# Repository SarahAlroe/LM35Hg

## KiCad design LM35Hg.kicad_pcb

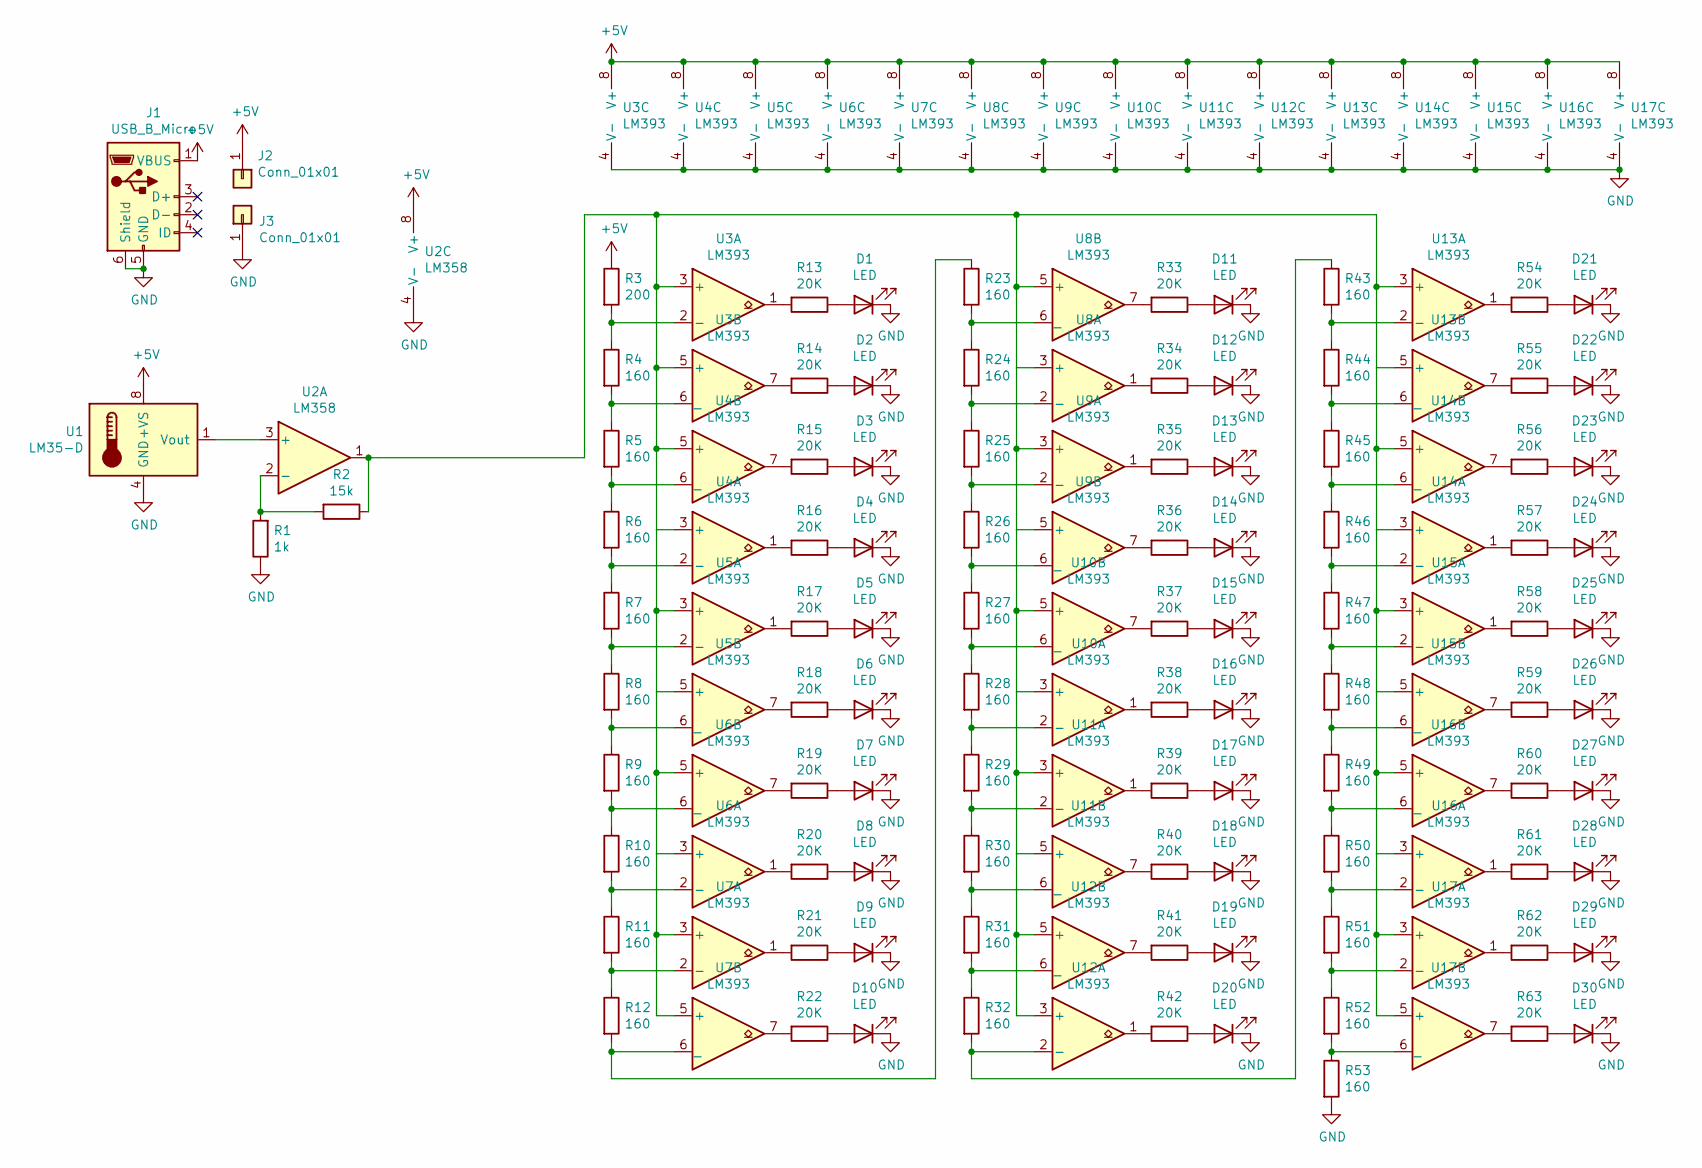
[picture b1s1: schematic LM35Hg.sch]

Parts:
D1, D2, D3, D4, D5, D6, D7, D8, D9, D10, D11, D12, D13, D14, D15, D16, D17, D18, D19, D20, D21, D22, D23, D24, D25, D26, D27, D28, D29, D30: LED; R_1206_3216Metric
J1: USB_B_Micro; USB_Micro-B_Molex-105017-0001
J2, J3: Conn_01x01; PinSocket_1x01_P2.54mm_Vertical
R1: 1k; R_1206_3216Metric
R2: 15k; R_1206_3216Metric
R3: 200; R_1206_3216Metric
R4, R5, R6, R7, R8, R9, R10, R11, R12, R23, R24, R25, R26, R27, R28, R29, R30, R31, R32, R43, R44, R45, R46, R47, R48, R49, R50, R51, R52, R53: 160; R_1206_3216Metric
R13, R14, R15, R16, R17, R18, R19, R20, R21, R22, R33, R34, R35, R36, R37, R38, R39, R40, R41, R42, R54, R55, R56, R57, R58, R59, R60, R61, R62, R63: 20K; R_1206_3216Metric
U1: LM35-D; SOIC-8_3.9x4.9mm_P1.27mm
U2: LM358; SOP-8_3.9x4.9mm_P1.27mm
U3, U4, U5, U6, U7, U8, U9, U10, U11, U12, U13, U14, U15, U16, U17: LM393; SOP-8_3.9x4.9mm_P1.27mm

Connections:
+5V: J1.1 (VBUS), J2.1, R3.1, U1.8 (+VS), U2.8 (V+), U3.8 (V+), U4.8 (V+), U5.8 (V+), U6.8 (V+), U7.8 (V+), U8.8 (V+), U9.8 (V+), U10.8 (V+), U11.8 (V+), U12.8 (V+), U13.8 (V+), U14.8 (V+), U15.8 (V+), U16.8 (V+), U17.8 (V+)
GND: D1.1 (K), D2.1 (K), D3.1 (K), D4.1 (K), D5.1 (K), D6.1 (K), D7.1 (K), D8.1 (K), D9.1 (K), D10.1 (K), D11.1 (K), D12.1 (K), D13.1 (K), D14.1 (K), D15.1 (K), D16.1 (K), D17.1 (K), D18.1 (K), D19.1 (K), D20.1 (K), D21.1 (K), D22.1 (K), D23.1 (K), D24.1 (K), D25.1 (K), D26.1 (K), D27.1 (K), D28.1 (K), D29.1 (K), D30.1 (K), J1.5 (GND), J1.6 (Shield), J3.1, R1.1, R53.2, U1.4 (GND), U2.4 (V-), U3.4 (V-), U4.4 (V-), U5.4 (V-), U6.4 (V-), U7.4 (V-), U8.4 (V-), U9.4 (V-), U10.4 (V-), U11.4 (V-), U12.4 (V-), U13.4 (V-), U14.4 (V-), U15.4 (V-), U16.4 (V-), U17.4 (V-)
unnamed: D1.2 (A), R13.1
unnamed: D2.2 (A), R14.1
unnamed: D3.2 (A), R15.1
unnamed: D4.2 (A), R16.1
unnamed: D5.2 (A), R17.1
unnamed: D6.2 (A), R18.1
unnamed: D7.2 (A), R19.1
unnamed: D8.2 (A), R20.1
unnamed: D9.2 (A), R21.1
unnamed: D10.2 (A), R22.1
unnamed: D11.2 (A), R33.1
unnamed: D12.2 (A), R34.1
unnamed: D13.2 (A), R35.1
unnamed: D14.2 (A), R36.1
unnamed: D15.2 (A), R37.1
unnamed: D16.2 (A), R38.1
unnamed: D17.2 (A), R39.1
unnamed: D18.2 (A), R40.1
unnamed: D19.2 (A), R41.1
unnamed: D20.2 (A), R42.1
unnamed: D21.2 (A), R54.1
unnamed: D22.2 (A), R55.1
unnamed: D23.2 (A), R56.1
unnamed: D24.2 (A), R57.1
unnamed: D25.2 (A), R58.1
unnamed: D26.2 (A), R59.1
unnamed: D27.2 (A), R60.1
unnamed: D28.2 (A), R61.1
unnamed: D29.2 (A), R62.1
unnamed: D30.2 (A), R63.1
unnamed: R1.2, R2.2, U2.2 (-)
unnamed: R2.1, U2.1, U3.3 (+), U3.5 (+), U4.3 (+), U4.5 (+), U5.3 (+), U5.5 (+), U6.3 (+), U6.5 (+), U7.3 (+), U7.5 (+), U8.3 (+), U8.5 (+), U9.3 (+), U9.5 (+), U10.3 (+), U10.5 (+), U11.3 (+), U11.5 (+), U12.3 (+), U12.5 (+), U13.3 (+), U13.5 (+), U14.3 (+), U14.5 (+), U15.3 (+), U15.5 (+), U16.3 (+), U16.5 (+), U17.3 (+), U17.5 (+)
unnamed: R3.2, R4.1, U3.2 (-)
unnamed: R4.2, R5.1, U3.6 (_)
unnamed: R5.2, R6.1, U4.6 (_)
unnamed: R6.2, R7.1, U4.2 (-)
unnamed: R7.2, R8.1, U5.2 (-)
unnamed: R8.2, R9.1, U5.6 (_)
unnamed: R9.2, R10.1, U6.6 (_)
unnamed: R10.2, R11.1, U6.2 (-)
unnamed: R11.2, R12.1, U7.2 (-)
unnamed: R12.2, R23.1, U7.6 (_)
unnamed: R13.2, U3.1
unnamed: R14.2, U3.7
unnamed: R15.2, U4.7
unnamed: R16.2, U4.1
unnamed: R17.2, U5.1
unnamed: R18.2, U5.7
unnamed: R19.2, U6.7
unnamed: R20.2, U6.1
unnamed: R21.2, U7.1
unnamed: R22.2, U7.7
unnamed: R23.2, R24.1, U8.6 (_)
unnamed: R24.2, R25.1, U8.2 (-)
unnamed: R25.2, R26.1, U9.2 (-)
unnamed: R26.2, R27.1, U9.6 (_)
unnamed: R27.2, R28.1, U10.6 (_)
unnamed: R28.2, R29.1, U10.2 (-)
unnamed: R29.2, R30.1, U11.2 (-)
unnamed: R30.2, R31.1, U11.6 (_)
unnamed: R31.2, R32.1, U12.6 (_)
unnamed: R32.2, R43.1, U12.2 (-)
unnamed: R33.2, U8.7
unnamed: R34.2, U8.1
unnamed: R35.2, U9.1
unnamed: R36.2, U9.7
unnamed: R37.2, U10.7
unnamed: R38.2, U10.1
unnamed: R39.2, U11.1
unnamed: R40.2, U11.7
unnamed: R41.2, U12.7
unnamed: R42.2, U12.1
unnamed: R43.2, R44.1, U13.2 (-)
unnamed: R44.2, R45.1, U13.6 (_)
unnamed: R45.2, R46.1, U14.6 (_)
unnamed: R46.2, R47.1, U14.2 (-)
unnamed: R47.2, R48.1, U15.2 (-)
unnamed: R48.2, R49.1, U15.6 (_)
unnamed: R49.2, R50.1, U16.6 (_)
unnamed: R50.2, R51.1, U16.2 (-)
unnamed: R51.2, R52.1, U17.2 (-)
unnamed: R52.2, R53.1, U17.6 (_)
unnamed: R54.2, U13.1
unnamed: R55.2, U13.7
unnamed: R56.2, U14.7
unnamed: R57.2, U14.1
unnamed: R58.2, U15.1
unnamed: R59.2, U15.7
unnamed: R60.2, U16.7
unnamed: R61.2, U16.1
unnamed: R62.2, U17.1
unnamed: R63.2, U17.7
unnamed: U1.1 (Vout), U2.3 (+)

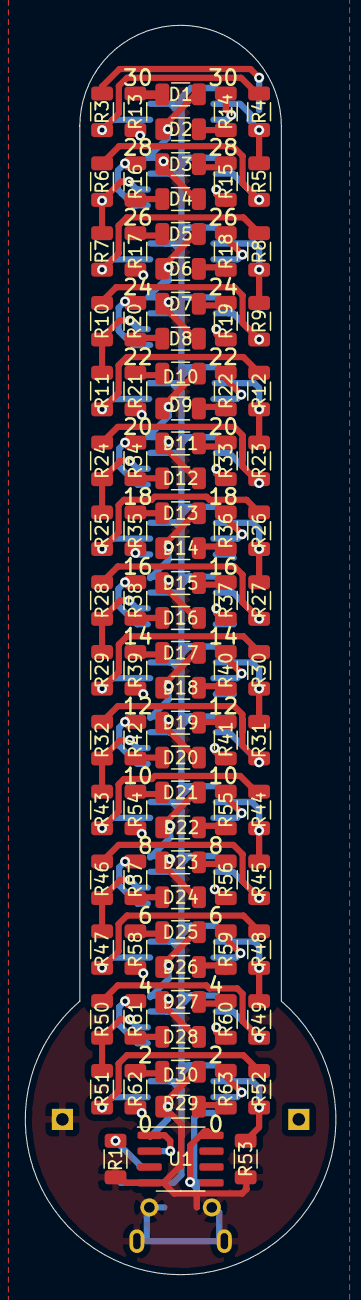
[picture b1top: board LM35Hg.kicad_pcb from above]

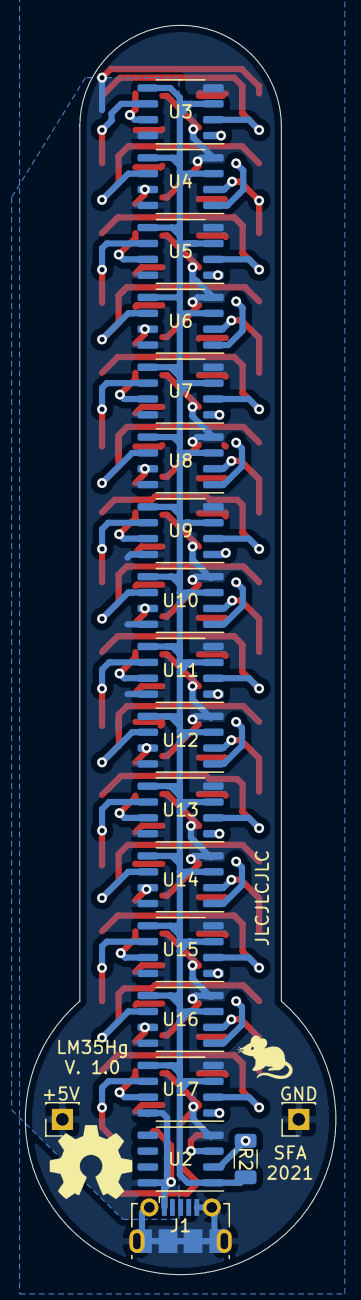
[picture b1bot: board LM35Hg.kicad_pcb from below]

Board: 2 copper layers, 24.9 x 100.0 mm, 113 parts (20 on the bottom side), 95 nets.

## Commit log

2021-06-09 Init
